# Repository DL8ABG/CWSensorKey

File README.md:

# Introduction #

This project contains a kit for a CW-key (or morse key) that works without any mechanical parts but is based on electronic sensors. The idea and initial designs comes from [John, M0UKD](https://m0ukd.com/homebrew/capacitive-cw-touch-key-circuits/) and is extended within this project to a complete kit with housing and a construction of a CW sensor pad.

Credits:
- [John, M0UKD](https://m0ukd.com/homebrew/capacitive-cw-touch-key-circuits/) for the great idea and documentation of this tiny circuit
- [Ken, KM4NFQ](https://github.com/km4nfq/capacitive-touch-key) for his design of the circuit board in [KiCad](https://www.kicad.org/), which was the starting point and inspiration for me on this kit
- Stephan, DO2WWW, for his support during the development of this kit
- [Christian, DJ9PH](https://www.qrz.com/db/DJ9PH), for his support during the development of this kit and for designing the housing for 3D printing. It looks great! He also supported the official setup of the kit by the [AATIS](https://www.aatis.de).

# Available as a kit #

The key and the 3D printed housing are available as kit from AATIS as set number [AS686](https://www.aatis.de).

## pieces needed for the complete kit ##

To assemble the complete kit, you need this:
- the fully assembled electronics board (see "[Electronics](#electronics)" section below)
- the assembled CW Sensor Pad (see "[The CW sensor pad](#the-cw-sensor-pad)" section below)
- housing:
  - metal housing Mammond 1550Q see below ["metal Housing"](#metal-housing)
  - 3D printed housing, see below ["3D printed Housing"](#3d-printed-housing)
- 1 holder for 2 batteries AAA (e.g. from [Reichelt](https://www.reichelt.de/de/de/shop/produkt/batteriehalter_fuer_2_microzellen_aaa_loetfahnen-57125))
- 1 switch (e.g. from [Reichelt](https://www.reichelt.de/de/de/shop/produkt/miniatur-kippschalter_ein-aus_3_a_125_v-359360))
- 1 stereo jack for 3,5mm (e.g. from [Reichelt](https://www.reichelt.de/de/de/shop/produkt/klinkeneinbaubuchse_3_5_mm_stereo-7301))
- material for mounting (see ["Options for mounting"](#options-for-mounting) below)

# Electronics #
The board used in this project was initially designed by [John, M0UKD](https://m0ukd.com/homebrew/capacitive-cw-touch-key-circuits/) and the [KiCad](https://www.kicad.org/) file is based on the work of [Ken, KM4NFQ](https://github.com/km4nfq/capacitive-touch-key). It was changed in shape to fit in the housing and make the wiring easy. 

## Bill of electronic parts ##
- 1 x circuit board
- 2 x IRFML8244TRPBF MOSFETs, SMD SOT-23 (Q1, Q2)
- 2 x AT42QT1011 Touch sensors, SMD (U1, U2)
- 2 x 22K Ohm resistors, SMD 1206 (R1, R2)
- 2 x 0.1uF capacitors, SMD 1206 (C1, C3)
- 2 x 2.2nF capacitors, SMD 1206 (C2, C4)

## Building the circuit board ##

During the soldering, be careful due to the small size of the board and parts, not to make short circuits or bridges of solder. Beyond that and due to the small amount of parts, the soldering is an easy thing.

There are some vias in the board to ensure the GND level to be reliability available on all places needed. The back of the board is connected to GND (except the small places for connecting the wires).

The circuit board from the solder side looks like this (picture generated with KiCad):

The circuit board from the bottom side looks like this (picture generated with KiCad):

The schematic it identical to that of [M0UKD](https://m0ukd.com/homebrew/capacitive-cw-touch-key-circuits/):

## Wiring ##

The board has connectors (with its markings on the bottom side which is later visible during installation in the housing): 
- for the sensor pad, marked with I for dit and A for dah
- for the connector, marked with T for tip, R for ring and G for ground of the 3 pin 3,5mm plug
- power supply, marked with + and -

All electrical parts together look like this:

You see the battery holder mounted on the bottom side of the board and the switch is inserted in the + cord.

# Mechanics #

## The CW sensor pad ##
The pad is designed to use coins as sensor fields. For Germany/Europe Euro coins are easily accessible. That was the reason, why 10 Euro-Cent coins will fit in the sensor (diameter 19.75mm, width nearly 2mm). If you intend to use other dimensions, adapt the [FreeCAD](https://www.freecad.org/) files as needed.

The sensor pad consists of multiple pieces of 2mm wood to be cut by e.g. a laser cutter. In the development of this kit I found, that the "2mm" plates are only 1.9 mm in with, so the holes for fitting together the single plates are designed for this width. If you have really 2.0 mm wide plates, use a file or a piece of sand paper to adjust the width of the holes to your need.

The sensor pad consists of 6 pieces of wood:
- 2 rectangular holder plates
- 2 middle plates which differ in the position of the "wire channel" from each other
- 2 side plates with round holes to fit the coins

First step:
- glue together the 2 rectangular holders
- glue together the 2 middle plates

Take care that the each two pieces lie exactly on top of each other!

After having glued the first parts, it should look like this:

Now glue the side plates on each side of the middle plates. Also here, take care that they lie exactly in the right position.

Now you have two pieces:

Now set the holder in the hole at the end of the pad. Take care, that it is directly connected to the back side of the side plates. This ensures the correct alignment in up/down direction. Also take care, that the sensor pad part and the holder have a good rectangular orientation to ensure a correct alignment to the left and right.

Your assembled sensor pad should look like this:

The next step is to prepare the coins. Solder the wires on them (next to the edge). The solder spot should be not to big (it must fit in the small hole below the coin in the pad). Prior to soldering, clean the surface of the coin on the place you want to solder with a screwdriver to remove the oxide layer that normally covers the coin.
It should look like this at the end of this step:

Now insert the wires in the small holes below the holders of the coins, so that they exit the pad at the back side. The coins should fit perfectly in the holder plates and it should look like this. If there are residue of the glue in the holes for the wires, clean them with a thin drill.

Glue the coins in the holder plates and/or use some plastic tape to prevent them from falling out. With that, your sensor pad is complete and can be installed in the housing.

## Metal housing ##

For a metal housing, you need the following components:
- the housing Mammond 1550Q (e.g. from [Reichelt](https://www.reichelt.de/de/de/shop/produkt/alugehaeuse_1550_q_60_x_55_x_30_mm_aluminium-221407))
- 4 distance bolts M2,5 with length 5mm (e.g. from [Reichelt](https://www.reichelt.de/de/de/shop/produkt/distanzbolzen_5_mm_m2_5-236284))
- 4 screws M2,5 x 5mm
- 8 washers for M2,5
- 8 lock washers for M2,5
- 4 nut screws M2,5

- for mounting the CW Sensor Pad, you need:
  - 2 screws M3 x 10mm
  - 2 washers for M3
  - 2 lock washers for M3
  - 2 nut screws for M3

Preparing the Mammond 1550Q

### Hole for sensor paddle ###

First mark the middle of the _wider_ side (green on the next picture).

Than mark nearly 2mm to each side (blue on the next picture). In sum it must meet the width of your paddle. It is ok, if it is a tight fit.
The hight of the marking is 23mm to meet the height of the paddle.

Than take a metal saw to cut out the opening along the outer lines (the blue ones in the picture above). Use a key file to make the opening accurately rectangular.

Next mark the hole for the paddle holder. You can measure it (12mm from the bottom and 30mm apart). To make sure it fits with your holder, additionally place the holder it the opening you just prepared and use the holes in the wooden plates to mark points for the holes (or verify your measurement).

Than drill the holes to fit with the 3mm screws. If you use countersunk screws, also drill the lowering.

### Holes for the board ###

Place the paddle in its position (you can also use the screws to temporarily holt it in place). Than lay the circuit board inside the housing and position it so that the holder of the paddle protrudes into the recess.

To have enough room for the switch and connector at the back side, place the circuit board as tight as possible next to the paddle holder.

Mark the points for the holes and drill them to fit the 2.5mm screws. As well here: if you use countersunk screws, also drill the lowering.

### Holes for connector and switch ###

The positioning of the holes for the connection and the switch is somewhat difficult. 

Depending of the parts you use, they can either be positions on the side next to the circuit board or you can position the connector centered "above" the circuit board and only the switch side next of it.

Be careful to leave enough space for the circuit board with the bolts holding it and the batterie holder, which is placed on top of the circuit board.

This picture shows the installation side next to the board (on one of the prototypes):

This picture shows the holes for the connector centered and the switch at the side:

So you can place it as you like it best. For example: according to the hand you want to use the key, place the switch on the side "away" from you to have it out of your way during usage.

### Putting the pieces in the metal housing ###
Here you see the suggested mounting order seen on the third prototype. How to find the places for the holes in the housing will be explained here in a later version of the README.

First set the bolts for holding the board in the housing using lock washers to keep it tight:

Second fix the board on the bolts with the nuts (including washers):

Then fix the sensor pad, the connector and the switch in its holes:

As the last step, mount the battery holder on the board. 

There are two options:
- using some double-sided adhesive tape: Use strong adhesive tape, preferably one with a layer of silicone, which is often recommended for outdoor use.
- use the hole in the center of the board to screw the battery holder to the board. Therefore, you need an _additional_ M2.5 screw with plate, washer plate and nut (not mentioned in the part list on top of the page)

Now you can close the housing and your key is complete (or you want to add magnets as a mounting option, what ist explained in the next section).

## 3D printed housing ##

For the 3D printed housing you need the following:
- 3D printed housing, a bottom and a top part (files to be found under mechanics/housing)
- 12 press-fit sleeves M3
  - 4 of them only if you want to attach magnets below the hosing (see ["Options for mounting"](#options-for-mounting) below)
- 4 screws M3 x 8mm (holding the circuit board)
- 4 screws M3 x min 10mm (connecting the two parts of the hosing)

- for mounting the CW Sensor Pad, you need:
  - 2 screws M3 x 10mm
  - 2 washers for M3
  - 2 lock washers for M3
  - 2 nut screws for M3

The wiring is identical to that when using the metal housing.

### The press-fit sleeves ###

First, the press-fit sleeves must be installed. It is recommend to use an installation aid to ensure that they are pressed in straight. If this is not available, please use a conical soldering iron tip and hold it absolutely straight.

The press-in nuts of the magnet should also be pressed in from the INSIDE to ensure a secure hold.

### The sensor pad ###

The sensor pad is inserted in the rectangular hole in the same way as for the metal housing. The screws are inserted from the outside with plates and washer plates and nuts inside. 

### The electronics ###

This step is similar to that of the metal housing:
- mount the battery holder on the circuit board
- mount both inside the housing using 4 screws

### Connector and switch ###

The holes are prepared in the 3D printed housing. Just insert them and use their screws to fixate them. Some force is needed to make them hold. Be careful that it is tight enough but not to tight to damage them.

## Options for mounting ##
As the kit is intended for universal use, you can decide for which purpose you like to use it in your case. It can be used for portable operation (due to its small size and good closure thus resistance against dirt) or for use in your shack.

For portable use, you can mount strong magnets on the bottom side of the housing. With them you can attach the key to any (magnetic) surface you like (your portable TRX, a metal case, ...). This is the way, many portable keys work (like those from [Palm](https://www.eham.net/reviews/view-product/11153) or other companies).

Possible sources for the magnets are (listed as *examples*)
- [Supermagnete](https://www.supermagnete.de/neodym-magnete-zum-anschrauben/quadermagnet-zum-anschrauben-40-x-20-x-4mm_CS-Q-40-20-04-N)
- [Amazon](https://www.amazon.de/dp/B08F54YGC9)

This is, how it can look:

For use only in your shack, you can mount the bottom side of the key directly to a heavy item like a metal plate (e.g. steal with 8cm x 8cm x 2cm) or a stone plate, with probably looks great). For this mounting, you drill holes according to the holes for the screws in the housing through yor item and replace the screws of the housing with longer ones suitable for your item dimension. In this way you mount your item, the bottom of the housing and the top of the housing in once.

# Hints #
## Battery falling out of holder when mounting the key with strong magnets ##

If you have very strong magnets, it can happen, that the batteries fall out of its holder if you attach the key to a surface. To avoid this, put some foam on top of the batteries to tighten their position together with the bottom of the housing.

# History #

## First Prototype ##
The first prototype is shown here. It was my first try on how good the circuit works and was made by parts I found after receiving the board. I also verified with this construction, that coins are suitable sensor pads (here 5 Euro-Cent coins).

## Second Prototype ##
I changed the first prototype by replacing the "testing" sensor pad with first example made from laser cutted wood.

## Third prototype ##
After some changes to the board to reduce its size and place the solder pads on either sides, the third prototype became available. Here you see its construction.

This is the electronic connected with all external components:

This is the same showing the bottom side of the board (where the battery holder is glued on):

And theses are pictures of the whole key in its housing:

## Version 4 ##
As this is more than an "prototype" I call ist version 4 ;-)

# Responsibility #
This kit is build by **you**. You are responsible for all safety and legal aspects on setup and operation!! 

The author is not liable for anything, as he only shows his ideas on how such a sensor key can be build.

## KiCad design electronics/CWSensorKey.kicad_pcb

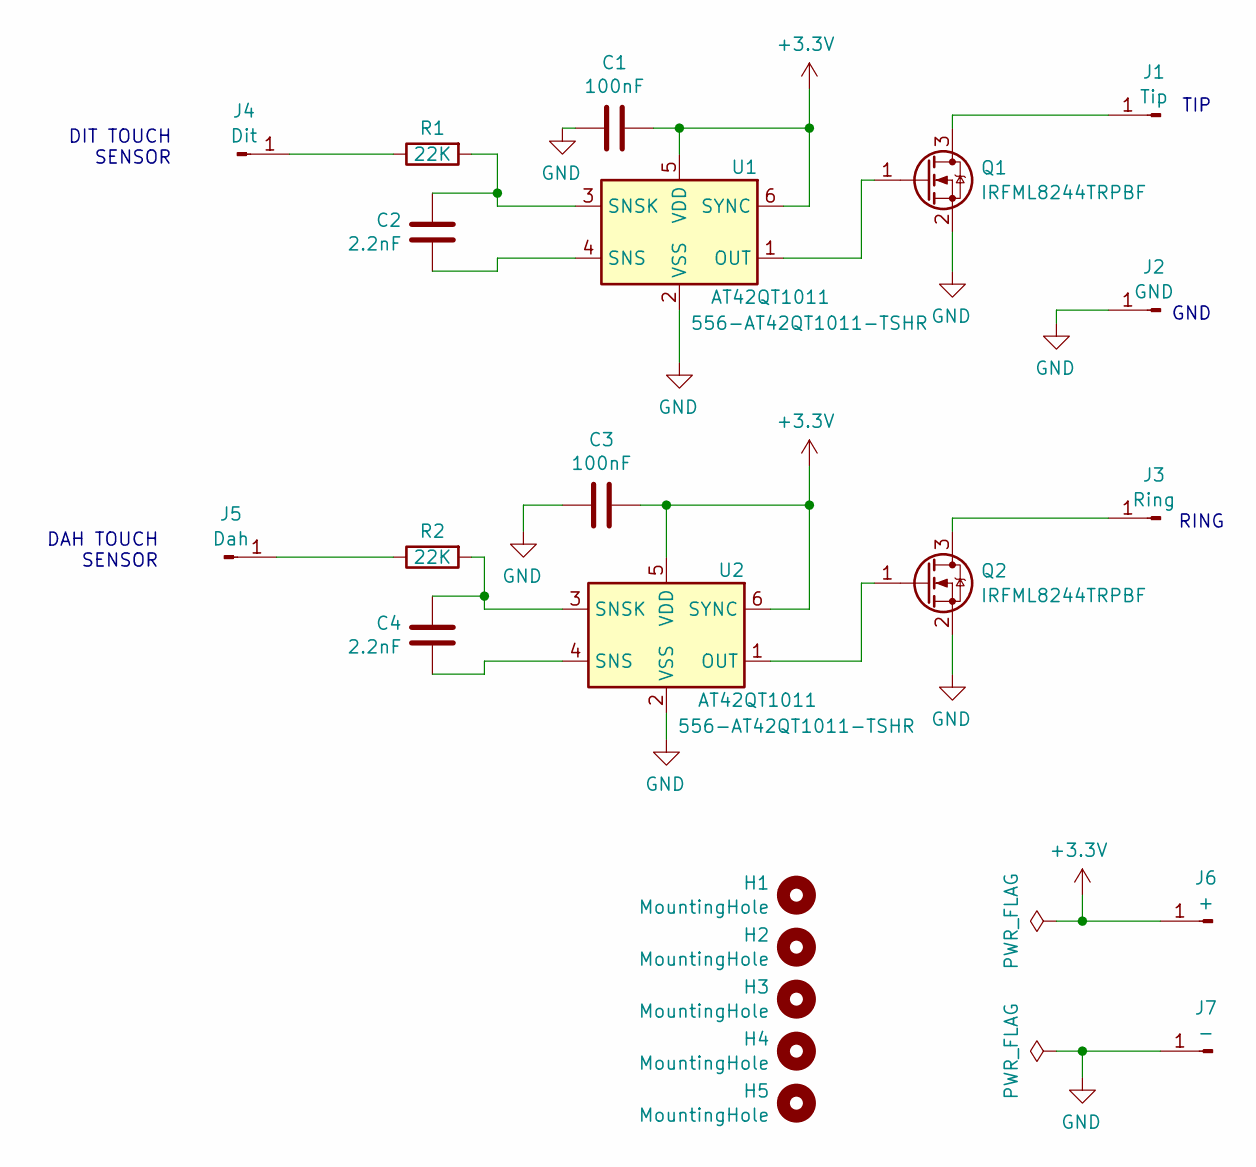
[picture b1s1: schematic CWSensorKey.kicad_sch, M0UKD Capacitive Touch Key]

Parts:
C1, C3: 100nF; C_1210_3225Metric_Pad1.33x2.70mm_HandSolder
C2, C4: 2.2nF; C_1210_3225Metric_Pad1.33x2.70mm_HandSolder
H1, H2, H3, H4, H5: MountingHole; MountingHole_3mm
J1: Tip; PinHeader_1x01_P2.54mm_Vertical
J2: GND; PinHeader_1x01_P2.54mm_Vertical
J3: Ring; PinHeader_1x01_P2.54mm_Vertical
J4: Dit; PinHeader_1x01_P2.54mm_Vertical
J5: Dah; PinHeader_1x01_P2.54mm_Vertical
J6: +; PinHeader_1x01_P2.54mm_Vertical
J7: -; PinHeader_1x01_P2.54mm_Vertical
Q1, Q2: IRFML8244TRPBF; SOT-23_Handsoldering
R1, R2: 22K; C_1206_3216Metric_Pad1.33x1.80mm_HandSolder
U1, U2: AT42QT1011; SOT-23-6_Handsoldering

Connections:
+3.3V: C1.2, C3.2, J6.1, U1.5 (VDD), U1.6 (SYNC), U2.5 (VDD), U2.6 (SYNC)
GND: C1.1, C3.1, J2.1, J7.1, Q1.2 (S), Q2.2 (S), U1.2 (VSS), U2.2 (VSS)
unnamed: J1.1, Q1.3 (D)
unnamed: J3.1, Q2.3 (D)
unnamed: J4.1, R1.1
unnamed: J5.1, R2.1
unnamed: Q1.1 (G), U1.1 (OUT)
unnamed: Q2.1 (G), U2.1 (OUT)
unnamed: C2.2, U1.4 (SNS)
unnamed: C2.1, R1.2, U1.3 (SNSK)
unnamed: C4.2, U2.4 (SNS)
unnamed: C4.1, R2.2, U2.3 (SNSK)

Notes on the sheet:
GND
DAH TOUCH SENSOR
TIP
RING
DIT TOUCH SENSOR

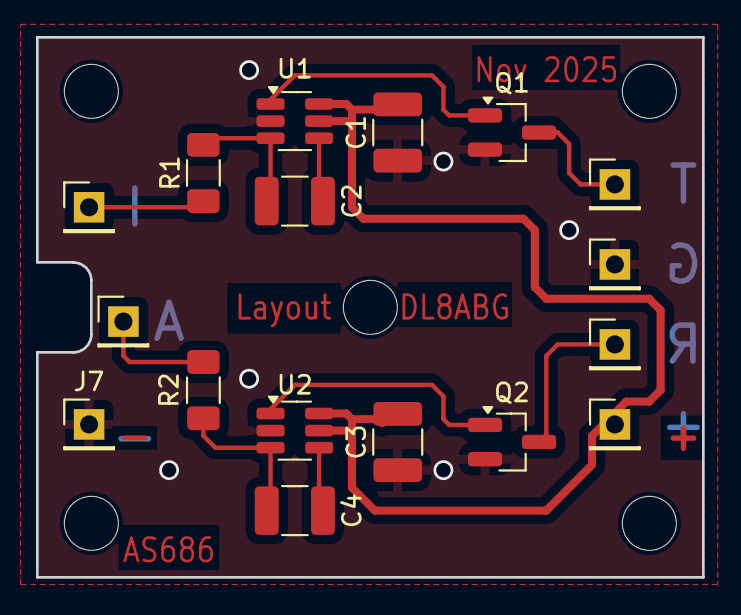
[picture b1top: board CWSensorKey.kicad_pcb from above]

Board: 2 copper layers, 37.0 x 30.0 mm, 22 parts (0 on the bottom side), 12 nets.

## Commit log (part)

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2025-05-17 Added first files
2025-05-17 Corrected formatting of README.md
2025-05-17 Further corrections in README.md
2025-05-17 and further changes on README.md
2025-05-23 Changed CW-Pad and added script for 2D generation in FreeCAD
2025-05-23 Changed holder to fit in housing
2025-05-23 generated new gerbers files
2025-05-23 updated gitignore
2025-05-29 Extended Readme, slight changes to scripts and other parts
2025-05-29 Extended Readme
2025-05-29 Changed distance between screws in holder to a more convenient value. Typos in Readme
2025-05-30 Completed description on building the sensor pad. Added photo of the second prototype.
2025-05-30 Linking within Readme.md
2025-06-01 Further documentation in README.md Slightly changed dimensions of sensor pad Changed distance betw screws in sensor pad holder
2025-10-03 index on main: b7a867d Further documentation in README.md Slightly changed dimensions of sensor pad Changed distance betw screws in sensor pad holder
2025-10-03 Additional Information on third prototype and slight changes to the board
2025-10-03 index on main: b7a867d Further documentation in README.md Slightly changed dimensions of sensor pad Changed distance betw screws in sensor pad holder (#1)
2025-10-06 Adapted board for better fitting in the housing Implemented script for generation of all 2D files from the KiCad models
2025-10-06 Delete electronics/gerbers directory
    Resolved conflicts
2025-10-06 Delete electronics/gerbers directory
    resolving merge conflict
2025-10-06 Update CWSensorKey.kicad_prl
    updated active layer in kicad project file
2025-10-06 Branch (#3)
    * index on main: b7a867d Further documentation in README.md Slightly changed dimensions of sensor pad Changed distance betw screws in sensor pad holder
    * Adapted board for better fitting in the housing
    Implemented script for generation of all 2D files from the KiCad models
    * Delete electronics/gerbers directory
    resolving merge conflict
    * Update CWSensorKey.kicad_prl
2025-10-06 Regenerated gerber files for new board
2025-10-23 - Changed SMD resistors and capacitors to 1206 as this size is available within the kit from AATIS - Added picture of the board for better overview on github
2025-10-23 Zip of (old) gerber files removed
2025-10-25 Corrected wording and added advice on strong adhesive tape.
2025-11-01 - added option for mounting battery holder to board with screw - added information on AATIS kit number
2025-11-01 Updated date in schematic
2025-11-16 Cleaning up directory for mechanical components
2025-11-16 sorting things, where they belong :-)
2025-11-16 cleaning up unused file
2026-02-01 Further documentation and reorganisation of the files in mechanic directory
2026-02-01 even more documentation and an additional picture of the board
2026-02-01 slight changes (typos etc)
2026-02-01 added photos of the current version
2026-02-01 Formatting issues
2026-02-01 more formatting
